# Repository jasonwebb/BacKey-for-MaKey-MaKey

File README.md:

BacKey for MaKey MaKey
======

BacKey is a simple breakout board that clips onto the back of a MaKey MaKey and converts all of the female headers to alligator clip holes.

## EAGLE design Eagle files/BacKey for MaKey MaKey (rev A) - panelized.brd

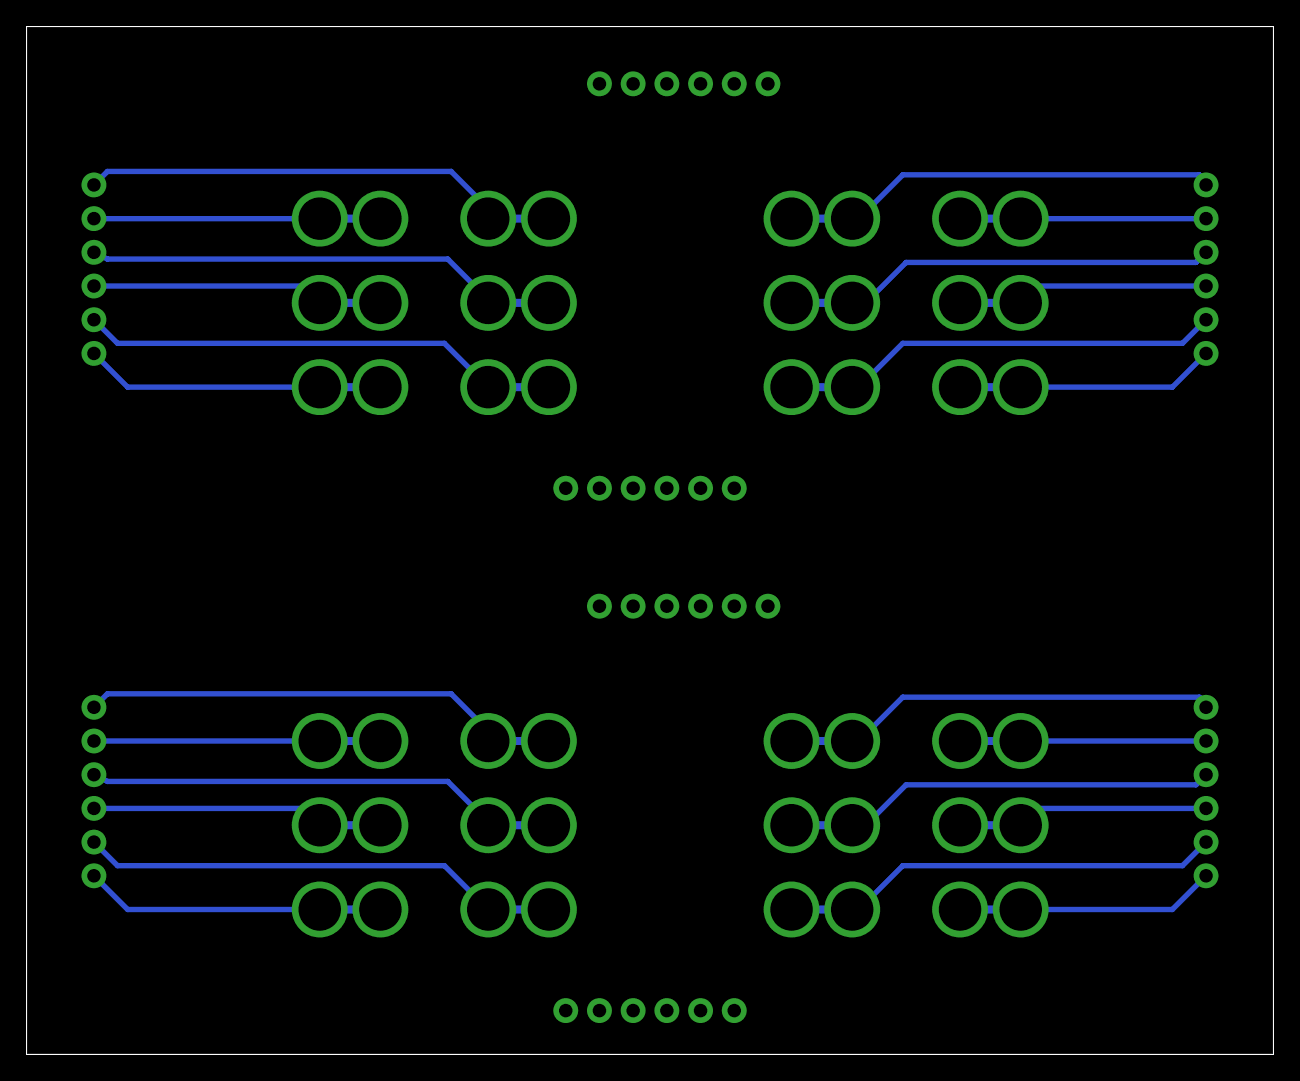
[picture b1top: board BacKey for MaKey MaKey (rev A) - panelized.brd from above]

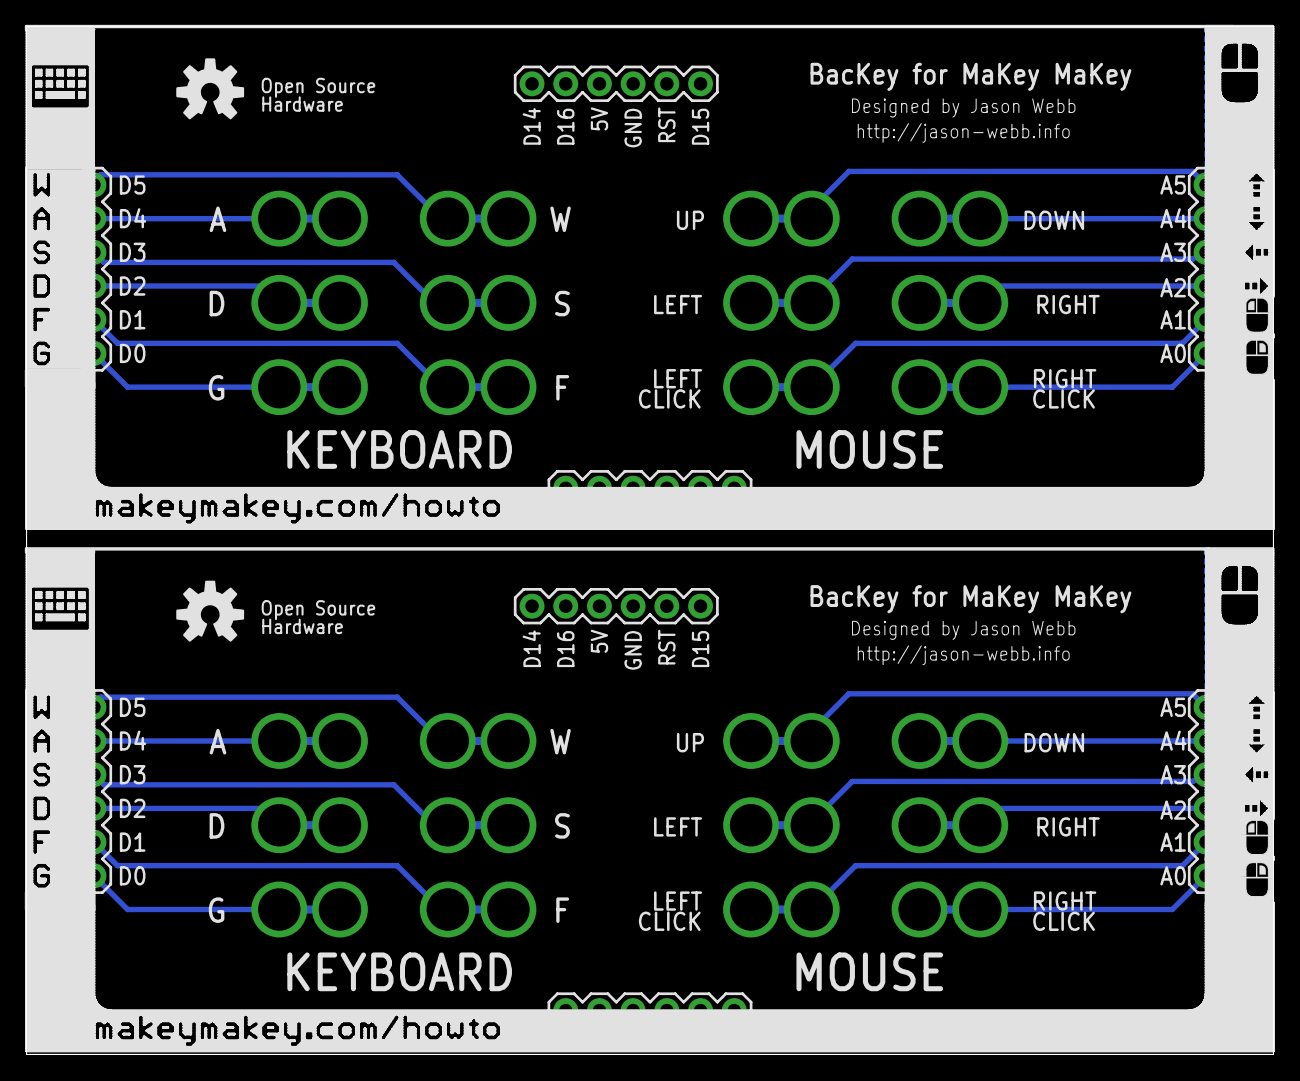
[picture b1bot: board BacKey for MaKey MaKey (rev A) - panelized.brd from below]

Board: 4 copper layers, 94.0 x 77.5 mm, 10 parts (10 on the bottom side), 2 nets.

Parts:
JP1, JP2, JP3, JP4, JP5, JP6, JP7, JP14: 1X06
U$1, U$2: OSHW-LOGOM; OSHW-LOGO-M

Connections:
GND: JP3.1, JP3.2, JP3.3, JP3.4, JP3.5, JP3.6, JP14.3
GND1: JP4.1, JP4.2, JP4.3, JP4.4, JP4.5, JP4.6, JP5.3

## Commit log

2013-11-23 Cleaned up schematic a bit

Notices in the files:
parts and their libraries:
SparkFun-Connectors: Licensing: CC v3.0 Share-Alike You are welcome to use this library for commercial purposes.
